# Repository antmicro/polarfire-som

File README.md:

# PolarFire SoM

Copyright (c) 2023-2025 [Antmicro](https://www.antmicro.com)

## Overview

This project contains open hardware design files for the Antmicro PolarFire System on Module (SoM) built around Microchip [PolarFire MPFS250T](https://www.microchip.com/en-us/product/mpfs250t) RISC-V System on Chip.
The SoM exposes two 100-pin high density connectors with signal assignment that is electrically compatible with [Raspberry Pi Compute Module 4](https://datasheets.raspberrypi.com/cm4/cm4-datasheet.pdf).

The PCB design files were prepared in KiCad 7.

## Key features

* PolarFire SoC MPFS250T
* 2 GB LPDDR4-1866 SDRAM
* 8 GB eMMC flash memory
* Compact size: 55x40mm 
* Gigabit Ethernet PHY (Ti/[DP83867ISRGZR](https://www.ti.com/lit/gpn/DP83867IS))
* 4-lane PCIe (via MPFS250T built-in XCVR transceivers)
* 2.4 GHz, 5.0 GHz IEEE 802.11 b/g/n/ac WiFi module (Murata/[LBEE5PK2AE](https://www.murata.com/en-eu/products/connectivitymodule/wi-fi-bluetooth/overview/lineup/type2ae))
* Bluetooth 5.2 module (Murata/LBEE5PK2AE)
* HDMI output
* 4-lane MIPI DSI and 4-lane MIPI CSI-2 exposed via Lattice [CrossLink](https://www.latticesemi.com/Products/FPGAandCPLD/CrossLink) (LIF-MD6000-6JMG80I) companion IC
* Additional 2-lane MIPI CSI-2 camera port, when working in 1.8V logic
* On-board power sequencing and voltage regulation based on a single 5V supply

## Project structure

The main directory contains KiCad PCB project files, a LICENSE, and a README.
The remaining files are stored in the following directories:

* `doc` - contains schematics in PDF format
* `assets` - contains visual assets for showcasing this design on [Open Hardware Portal](https://openhardware.antmicro.com).
* `img` - contains graphics for this README

## Licensing

This project is published under the [Apache-2.0](LICENSE) license.

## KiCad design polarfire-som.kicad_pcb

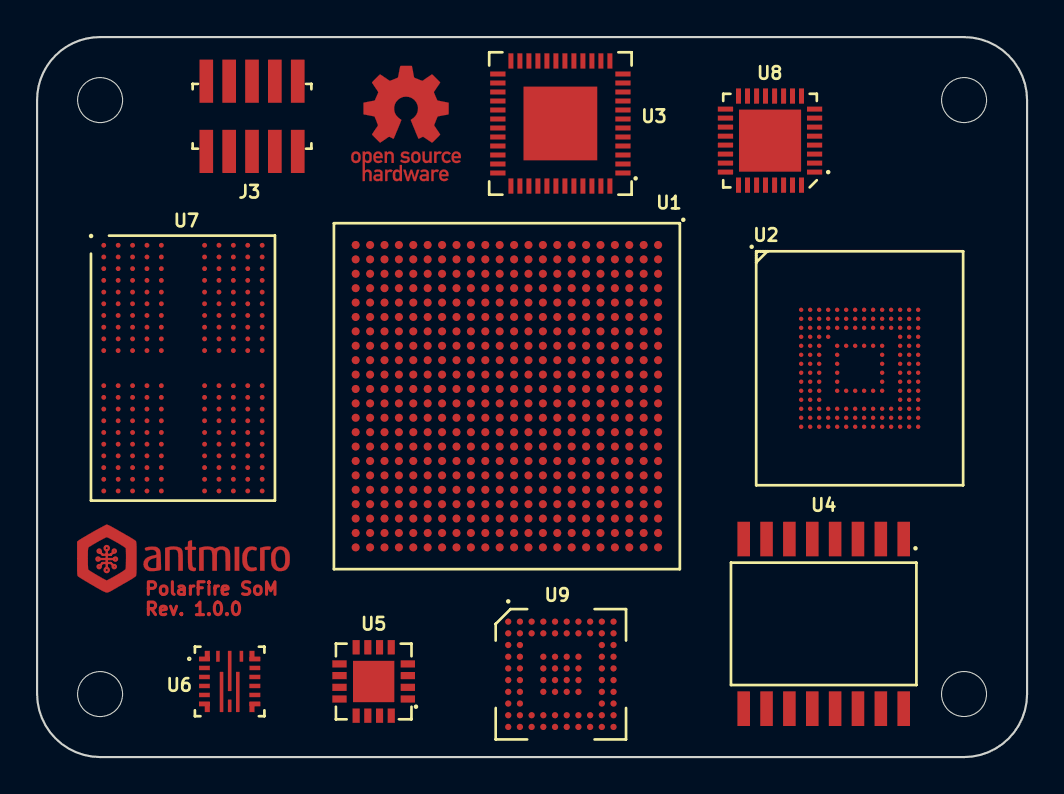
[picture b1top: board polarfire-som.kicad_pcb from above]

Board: 2 copper layers, 55.0 x 40.0 mm, 17 parts (1 on the bottom side), 211 nets, no tracks yet.

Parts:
J1: CM4_Plug_Module_Hirose_DF40_2x50_DF40C-100DP-0.4V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; CM4_Module_Conn_Plug_Hirose_DF40_2x50_DF40C-100DP-0.4V
J3: PinHeader_2x5_P1.27mm_SMD
MP1, MP2, MP3, MP4: MP_NPTH_Drill2.5mm
N1: antmicro_logo; antmicro-logo_scaled_12mm
N2: oshw_logo; oshw-logo
U1: MPFS250T-FCVG484; BGA-484_19x19mm_Layout22x22_P0.8mm_FCVG484
U2: SDINBDG4-8G; BGA-196-153_11.5x13mm_Layout14x14_P0.5x0.5mm
U3: DP83867ISRGZR; VQFN-48_7x7mm_P0.5mm_EP4.1x4.1mm
U4: MT25QL01GBBB8E_SOP2-16; SOP2-16_7.5x10.3mm
U5: PAC1934_QFN; QFN-16-1EP_4x4mm_P0.65mm
U6: TPS65296; VQFN-HR-18_3.5x3.5x1mm
U7: MT53D512M32D2_WFBGA; BGA-200_10.0x14.5mm_Layout12x22_P0.80x0.65mm
U8: USB3300-EZK-TR; QFN-32-1EP_5x5mm
U9: CrossLink_LIF-MD6000-6JMG80I; BGA-80_7x7mm_Layout10x10_P0.65mm

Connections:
/LPDDR4/LPDDR4_CA0_A: U1.T5 (MSS_DDR_A0), U7.H2 (CA0_A), U7.R2 (CA0_B)
/LPDDR4/LPDDR4_CA1_A: U1.T6 (MSS_DDR_A1), U7.J2 (CA1_A), U7.P2 (CA1_B)
/LPDDR4/LPDDR4_CA2_A: U1.V7 (MSS_DDR_A2), U7.H9 (CA2_A), U7.R9 (CA2_B)
/LPDDR4/LPDDR4_CA3_A: U1.V6 (MSS_DDR_A3), U7.H10 (CA3_A), U7.R10 (CA3_B)
/LPDDR4/LPDDR4_CA4_A: U1.R6 (MSS_DDR_A4), U7.H11 (CA4_A), U7.R11 (CA4_B)
/LPDDR4/LPDDR4_CA5_A: U1.R5 (MSS_DDR_A5), U7.J11 (CA5_A), U7.P11 (CA5_B)
/LPDDR4/LPDDR4_CKE0_A: U1.K1 (MSS_DDR_CKE0), U7.J4 (CKE0_A), U7.P4 (CKE0_B)
/LPDDR4/LPDDR4_CK_C_A: U1.U4 (MSS_DDR_CK_N0), U7.J9 (CK_c_A), U7.P9 (CK_c_B)
/LPDDR4/LPDDR4_CK_T_A: U1.U5 (MSS_DDR_CK0/DDR_PLL0_OUT0), U7.J8 (CK_t_A), U7.P8 (CK_t_B)
/LPDDR4/LPDDR4_CS0_A: U1.L3 (MSS_DDR_CS0), U7.H4 (CS0_A), U7.R4 (CS0_B)
/LPDDR4/LPDDR4_DMI0: U1.AB4 (MSS_DDR_DM0), U7.C3 (DMI0_A)
/LPDDR4/LPDDR4_DMI1: U1.AA7 (MSS_DDR_DM1), U7.C10 (DMI1_A)
/LPDDR4/LPDDR4_DMI2: U1.Y10 (MSS_DDR_DM2), U7.Y3 (DMI0_B)
/LPDDR4/LPDDR4_DMI3: U1.T10 (MSS_DDR_DM3), U7.Y10 (DMI1_B)
/LPDDR4/LPDDR4_DQ0: U1.Y3 (MSS_DDR_DQ0), U7.B2 (DQ0_A)
/LPDDR4/LPDDR4_DQ1: U1.Y4 (MSS_DDR_DQ1), U7.C2 (DQ1_A)
/LPDDR4/LPDDR4_DQ2: U1.Y1 (MSS_DDR_DQ2), U7.E2 (DQ2_A)
/LPDDR4/LPDDR4_DQ3: U1.AA1 (MSS_DDR_DQ3), U7.F2 (DQ3_A)
/LPDDR4/LPDDR4_DQ4: U1.Y5 (MSS_DDR_DQ4), U7.F4 (DQ4_A)
/LPDDR4/LPDDR4_DQ5: U1.AA5 (MSS_DDR_DQ5), U7.E4 (DQ5_A)
/LPDDR4/LPDDR4_DQ6: U1.AB2 (MSS_DDR_DQ6), U7.C4 (DQ6_A)
/LPDDR4/LPDDR4_DQ7: U1.AB3 (MSS_DDR_DQ7), U7.B4 (DQ7_A)
/LPDDR4/LPDDR4_DQ8: U1.W8 (MSS_DDR_DQ8), U7.B11 (DQ8_A)
/LPDDR4/LPDDR4_DQ9: U1.W7 (MSS_DDR_DQ9), U7.C11 (DQ9_A)
/LPDDR4/LPDDR4_DQ10: U1.AB5 (MSS_DDR_DQ10), U7.E11 (DQ10_A)
/LPDDR4/LPDDR4_DQ11: U1.AA6 (MSS_DDR_DQ11), U7.F11 (DQ11_A)
/LPDDR4/LPDDR4_DQ12: U1.AB7 (MSS_DDR_DQ12), U7.F9 (DQ12_A)
/LPDDR4/LPDDR4_DQ13: U1.AB8 (MSS_DDR_DQ13), U7.E9 (DQ13_A)
/LPDDR4/LPDDR4_DQ14: U1.Y8 (MSS_DDR_DQ14), U7.C9 (DQ14_A)
/LPDDR4/LPDDR4_DQ15: U1.AA8 (MSS_DDR_DQ15), U7.B9 (DQ15_A)
/LPDDR4/LPDDR4_DQ16: U1.Y9 (MSS_DDR_DQ16), U7.AA2 (DQ0_B)
/LPDDR4/LPDDR4_DQ17: U1.W9 (MSS_DDR_DQ17), U7.Y2 (DQ1_B)
/LPDDR4/LPDDR4_DQ18: U1.AB9 (MSS_DDR_DQ18), U7.V2 (DQ2_B)
/LPDDR4/LPDDR4_DQ19: U1.AB10 (MSS_DDR_DQ19), U7.U2 (DQ3_B)
/LPDDR4/LPDDR4_DQ20: U1.V11 (MSS_DDR_DQ20), U7.U4 (DQ4_B)
/LPDDR4/LPDDR4_DQ21: U1.V10 (MSS_DDR_DQ21), U7.V4 (DQ5_B)
/LPDDR4/LPDDR4_DQ22: U1.Y11 (MSS_DDR_DQ22), U7.Y4 (DQ6_B)
/LPDDR4/LPDDR4_DQ23: U1.W11 (MSS_DDR_DQ23), U7.AA4 (DQ7_B)
/LPDDR4/LPDDR4_DQ24: U1.U8 (MSS_DDR_DQ24), U7.AA11 (DQ8_B)
/LPDDR4/LPDDR4_DQ25: U1.T8 (MSS_DDR_DQ25), U7.Y11 (DQ9_B)
/LPDDR4/LPDDR4_DQ26: U1.T11 (MSS_DDR_DQ26), U7.V11 (DQ10_B)
/LPDDR4/LPDDR4_DQ27: U1.U10 (MSS_DDR_DQ27), U7.U11 (DQ11_B)
/LPDDR4/LPDDR4_DQ28: U1.R11 (MSS_DDR_DQ28), U7.U9 (DQ12_B)
/LPDDR4/LPDDR4_DQ29: U1.R10 (MSS_DDR_DQ29), U7.V9 (DQ13_B)
/LPDDR4/LPDDR4_DQ30: U1.R8 (MSS_DDR_DQ30), U7.Y9 (DQ14_B)
/LPDDR4/LPDDR4_DQ31: U1.P8 (MSS_DDR_DQ31), U7.AA9 (DQ15_B)
/LPDDR4/LPDDR4_DQS0_N: U1.AA3 (MSS_DDR_DQS_N0), U7.E3 (DQS0_c_A)
/LPDDR4/LPDDR4_DQS0_P: U1.AA2 (MSS_DDR_DQS_P0), U7.D3 (DQS0_t_A)
/LPDDR4/LPDDR4_DQS1_N: U1.W6 (MSS_DDR_DQS_N1), U7.E10 (DQS1_c_A)
/LPDDR4/LPDDR4_DQS1_P: U1.Y6 (MSS_DDR_DQS_P1), U7.D10 (DQS1_t_A)
/LPDDR4/LPDDR4_DQS2_N: U1.AA10 (MSS_DDR_DQS_N2), U7.V3 (DQS0_c_B)
/LPDDR4/LPDDR4_DQS2_P: U1.AA11 (MSS_DDR_DQS_P2), U7.W3 (DQS0_t_B)
/LPDDR4/LPDDR4_DQS3_N: U1.V9 (MSS_DDR_DQS_N3), U7.V10 (DQS1_c_B)
/LPDDR4/LPDDR4_DQS3_P: U1.U9 (MSS_DDR_DQS_P3), U7.W10 (DQS1_t_B)
/LPDDR4/LPDDR4_ODT_CA_A: U1.L1 (MSS_DDR_ODT0), U7.G2 (ODT_CA_A), U7.T2 (ODT_CA_B)
/LPDDR4/LPDDR4_RESET_n: U1.L2 (MSS_DDR_RAM_RST_N/DDR_PLL0_OUT1), U7.T11 (RESET_n)
CAM1_C_N: J1.127, U9.A8 (DPHY0_CKN)
CAM1_C_P: J1.129, U9.B8 (DPHY0_CKP)
CAM1_D0_N: J1.115, U9.A7 (DPHY0_DN0)
CAM1_D0_P: J1.117, U9.B7 (DPHY0_DP0)
CAM1_D1_N: J1.121, U9.A9 (DPHY0_DN1)
CAM1_D1_P: J1.123, U9.B9 (DPHY0_DP1)
CAM1_D2_N: J1.133, U9.A6 (DPHY0_DN2)
CAM1_D2_P: J1.135, U9.B6 (DPHY0_DP2)
CAM1_D3_N: J1.139, U9.A10 (DPHY0_DN3)
CAM1_D3_P: J1.141, U9.B10 (DPHY0_DP3)
DSI1_C_N: J1.187, U9.A3 (DPHY1_CKN)
DSI1_C_P: J1.189, U9.B3 (DPHY1_CKP)
DSI1_D0_N: J1.175, U9.A2 (DPHY1_DN0)
DSI1_D0_P: J1.177, U9.B2 (DPHY1_DP0)
DSI1_D1_N: J1.181, U9.A4 (DPHY1_DN1)
DSI1_D1_P: J1.183, U9.B4 (DPHY1_DP1)
DSI1_D2_N: J1.193, U9.A1 (DPHY1_DN2)
DSI1_D2_P: J1.195, U9.B1 (DPHY1_DP2)
DSI1_D3_N: J1.194, U9.B5 (DPHY1_DP3)
DSI1_D3_P: J1.196, U9.A5 (DPHY1_DN3)
ETH_ TXRXM_C: J1.9, U3.8 (TD_M_C)
ETH_ TXRXM_D: J1.5, U3.11 (TD_M_D)
ETH_ TXRXP_B: J1.4, U3.4 (TD_P_B)
ETH_ TXRXP_D: J1.3, U3.10 (TD_P_D)
ETH_LED1: J1.15, U3.47 (LED_0)
ETH_LED2: J1.17, U3.46 (LED_1)
ETH_TXRXM_A: J1.10, U3.2 (TD_M_A)
ETH_TXRXM_B: J1.6, U3.5 (TD_M_B)
ETH_TXRXP_A: J1.12, U3.1 (TD_P_A)
ETH_TXRXP_C: J1.11, U3.7 (TD_P_C)
GND: J1.1, J1.2, J1.7, J1.8, J1.13, J1.14, J1.22, J1.23, J1.32, J1.33, J1.42, J1.43, J1.52, J1.53, J1.59, J1.60, J1.65, J1.71, J1.74, J1.98, J1.107, J1.108, J1.113, J1.114, J1.119, J1.120, J1.125, J1.126, J1.131, J1.132, J1.137, J1.138, J1.150, J1.155, J1.156, J1.161, J1.162, J1.167, J1.168, J1.173, J1.174, J1.179, J1.180, J1.185, J1.186
GPIO2: J1.58, U1.A8 (GPIO175PB1)
GPIO3: J1.56, U1.B8 (GPIO175NB1)
GPIO4: J1.54, U1.A6 (GPIO172PB1/CCC_SW_PLL1_OUT1)
GPIO5: J1.34, U1.C9 (GPIO176NB1/DQS)
GPIO6: J1.30, U1.D8 (GPIO174NB1)
GPIO7: J1.37, U1.H13 (GPIO185NB1)
GPIO8: J1.39, U1.H12 (GPIO182PB1/DQS)
GPIO9: J1.40, U1.G12 (GPIO182NB1/DQS)
GPIO10: J1.44, U1.D13 (GPIO2PB1/DQS)
GPIO11: J1.38, U1.C10 (GPIO176PB1/DQS/CCC_SW_PLL0_OUT0)
GPIO12: J1.31, U1.D9 (GPIO174PB1)
GPIO13: J1.28, U1.D6 (GPIO168NB1)
GPIO14: J1.55, U1.A7 (GPIO173PB1/CLKIN_S_3/CCC_SW_CLKIN_S_3)
GPIO15: J1.51, U1.H15 (GPIO7NB1)
GPIO16: J1.29, U1.C6 (GPIO171PB1/CLKIN_S_2/CCC_SW_CLKIN_S_2/C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)
GPIO17: J1.50, U1.H17 (GPIO8NB1/DQS)
GPIO18: J1.49, U1.G15 (GPIO7PB1)
GPIO19: J1.26, U1.B5 (GPIO170NB1/DQS)
GPIO20: J1.27, U1.C5 (GPIO170PB1/DQS/CCC_SW_PLL1_OUT0)
GPIO21: J1.25, U1.C4 (GPIO169PB1/CCC_SW_CLKIN_S_1)
GPIO22: J1.46, U1.F11 (GPIO181NB1)
GPIO23: J1.47, U1.F16 (GPIO11NB1)
GPIO24: J1.45, U1.D14 (GPIO2NB1/DQS)
GPIO25: J1.41, U1.E14 (GPIO9NB1)
GPIO26: J1.24, U1.B4 (GPIO169NB1)
GPIO27: J1.48, U1.G17 (GPIO8PB1/DQS/CCC_SE_PLL0_OUT0)
JTAG_RESET_n: J3.10, U1.H7 (DEVRST_N)
JTAG_TCK: J3.4, U1.E9 (TCK)
JTAG_TDI: J3.8, U1.G9 (TDI)
JTAG_TDO: J3.6, U1.E8 (TDO)
JTAG_TMS: J3.2, U1.F8 (TMS)
MSS_SGMII_RX0_N: U1.L6 (MSS_SGMII_RXN0), U3.36 (RX_D3_SGMII_SON)
MSS_SGMII_RX0_P: U1.L5 (MSS_SGMII_RXP0), U3.35 (RX_D2_SGMII_SOP)
MSS_SGMII_TX0_N: U1.N6 (MSS_SGMII_TXP0), U3.28 (TX_D0_SGMII_SIN)
MSS_SGMII_TX0_P: U1.N7 (MSS_SGMII_TXN0), U3.27 (TX_D1_SGMII_SIP)
unnamed: U1.A1 (VSS), U1.A4 (VSS), U1.A14 (VSS), U1.A22 (VSS), U1.AA4 (VSS), U1.AA14 (VSS), U1.AB1 (VSS), U1.AB11 (VSS), U1.AB22 (VSS), U1.B11 (VSS), U1.C8 (VSS), U1.C18 (VSS), U1.D5 (VSS), U1.D15 (VSS), U1.E2 (VSS), U1.E12 (VSS), U1.E20 (VSS), U1.E21 (VSS), U1.E22 (VSS), U1.F9 (VSS), U1.F18 (VSS), U1.F19 (VSS), U1.F20 (VSS), U1.G6 (VSS), U1.G16 (VSS), U1.G18 (VSS), U1.G22 (VSS), U1.H3 (VSS), U1.H20 (VSS), U1.J8 (VSS), U1.J10 (VSS), U1.J12 (VSS), U1.J14 (VSS), U1.J16 (VSS), U1.J22 (VSS), U1.K9 (VSS), U1.K11 (VSS), U1.K13 (VSS), U1.K15 (VSS), U1.K17 (VSS), U1.K20 (VSS), U1.L4 (VSS), U1.L10 (VSS), U1.L12 (VSS), U1.L14 (VSS), U1.L16 (VSS), U1.L18 (VSS), U1.L22 (VSS), U1.M1 (VSS), U1.M9 (VSS), U1.M11 (VSS), U1.M13 (VSS), U1.M15 (VSS), U1.M17 (VSS), U1.M19 (VSS), U1.M20 (VSS), U1.N10 (VSS), U1.N12 (VSS), U1.N14 (VSS), U1.N16 (VSS), U1.N18 (VSS), U1.N22 (VSS), U1.P5 (VSS), U1.P9 (VSS), U1.P11 (VSS), U1.P13 (VSS), U1.P15 (VSS), U1.P17 (VSS), U1.P20 (VSS), U1.R2 (VSS), U1.R18 (VSS), U1.R22 (VSS), U1.T9 (VSS), U1.T18 (VSS), U1.T19 (VSS), U1.T20 (VSS), U1.U6 (VSS), U1.U16 (VSS), U1.U20 (VSS), U1.U21 (VSS), U1.U22 (VSS), U1.V3 (VSS), U1.V13 (VSS), U1.W10 (VSS), U1.W20 (VSS), U1.Y7 (VSS), U1.Y17 (VSS)
unnamed: U1.A9 (VDDI1), U1.A19 (VDDI1), U1.B6 (VDDI1), U1.B16 (VDDI1), U1.C13 (VDDI1), U1.C21 (VDDI1), U1.D10 (VDDI1), U1.E17 (VDDI1), U1.F14 (VDDI1), U1.G11 (VDDI1)
unnamed: U1.AA9 (VDDI6), U1.AB6 (VDDI6), U1.N3 (VDDI6), U1.R7 (VDDI6), U1.T4 (VDDI6), U1.U1 (VDDI6), U1.U11 (VDDI6), U1.V8 (VDDI6), U1.W5 (VDDI6), U1.Y2 (VDDI6)
unnamed: U1.AA19 (VDDI0), U1.AB16 (VDDI0), U1.T14 (VDDI0), U1.V18 (VDDI0), U1.W15 (VDDI0), U1.Y12 (VDDI0), U1.Y22 (VDDI0)
unnamed: U1.C3 (VDDI2), U1.F4 (VDDI2), U1.G1 (VDDI2)
unnamed: U1.E7 (VDDI3), U1.J11 (VDDI3)
unnamed: U1.G21 (VDDA), U1.J21 (VDDA), U1.K19 (VDDA), U1.L21 (VDDA), U1.N21 (VDDA), U1.P19 (VDDA), U1.R21 (VDDA)
unnamed: U1.H8 (VDD25), U1.J17 (VDD25), U1.L15 (VDD25), U1.R9 (VDD25), U1.R17 (VDD25)
unnamed: U1.H14 (VDDAUX1), U1.H16 (VDDAUX1), U1.J9 (VDDAUX1), U1.J13 (VDDAUX1), U1.K10 (VDDAUX1)
unnamed: U1.H18 (XCVR_VREF), U1.H19 (XCVR_VREF)
unnamed: U1.J5 (VDDI4), U1.K2 (VDDI4)
unnamed: U1.J15 (VDD), U1.K12 (VDD), U1.K14 (VDD), U1.K16 (VDD), U1.L11 (VDD), U1.L13 (VDD), U1.L17 (VDD), U1.M12 (VDD), U1.M14 (VDD), U1.M16 (VDD), U1.N11 (VDD), U1.N13 (VDD), U1.N15 (VDD), U1.N17 (VDD)
unnamed: U1.J18 (VDDA25), U1.M18 (VDDA25)
unnamed: U1.K8 (VDDAUX2), U1.L9 (VDDAUX2)
unnamed: U1.K18 (VDD_XCVR_CLK), U1.P18 (VDD_XCVR_CLK)
unnamed: U1.M6 (VDDI5), U1.M8 (VDDI5)
unnamed: U1.M10 (VDDAUX4), U1.N9 (VDDAUX4)
unnamed: U1.P10 (VDD18), U1.P12 (VDD18), U1.P14 (VDD18), U1.P16 (VDD18), U1.R13 (VDD18)
unnamed: U2.A6 (VSS), U2.E7 (VSS), U2.G5 (VSS), U2.H10 (VSS), U2.J5 (VSS), U2.K8 (VSS)
unnamed: U2.C4 (VSSQ), U2.N2 (VSSQ), U2.N5 (VSSQ), U2.P4 (VSSQ), U2.P6 (VSSQ)
unnamed: U2.C6 (VCCQ), U2.M4 (VCCQ), U2.N4 (VCCQ), U2.P3 (VCCQ), U2.P5 (VCCQ)
unnamed: U2.E6 (VCC), U2.F5 (VCC), U2.J10 (VCC), U2.K9 (VCC)
unnamed: U3.3 (VDDA2P5), U3.9 (VDDA2P5)
unnamed: U3.13 (VDDA1P8), U3.48 (VDDA1P8)
unnamed: U3.19 (VDDIO), U3.30 (VDDIO), U3.41 (VDDIO)
unnamed: U3.6 (VDD1P0), U3.24 (VDD1P0), U3.31 (VDD1P0), U3.42 (VDD1P0)
unnamed: U7.A3 (VSS), U7.C1 (VSS), U7.C5 (VSS), U7.C8 (VSS), U7.D2 (VSS), U7.D4 (VSS), U7.D9 (VSS), U7.E1 (VSS), U7.E5 (VSS), U7.E8 (VSS), U7.G1 (VSS), U7.G3 (VSS), U7.G5 (VSS), U7.G8 (VSS), U7.J1 (VSS), U7.J3 (VSS), U7.K2 (VSS), U7.K4 (VSS), U7.K9 (VSS), U7.N2 (VSS), U7.N4 (VSS), U7.N9 (VSS), U7.P1 (VSS), U7.P3 (VSS), U7.T1 (VSS), U7.T3 (VSS), U7.T5 (VSS), U7.T8 (VSS)
unnamed: U7.A4 (VDD2), U7.A9 (VDD2), U7.F5 (VDD2), U7.F8 (VDD2), U7.H1 (VDD2), U7.H5 (VDD2), U7.H8 (VDD2), U7.K1 (VDD2), U7.K3 (VDD2), U7.N1 (VDD2), U7.N3 (VDD2), U7.R1 (VDD2), U7.R5 (VDD2), U7.R8 (VDD2)
unnamed: U7.A10 (VSS), U7.AB3 (VSS), U7.AB5 (VSS), U7.AB8 (VSS), U7.AB10 (VSS), U7.C12 (VSS), U7.D11 (VSS), U7.E12 (VSS), U7.G10 (VSS), U7.G12 (VSS), U7.J10 (VSS), U7.J12 (VSS), U7.K11 (VSS), U7.N11 (VSS), U7.P10 (VSS), U7.P12 (VSS), U7.T10 (VSS), U7.T12 (VSS), U7.V1 (VSS), U7.V5 (VSS), U7.V8 (VSS), U7.V12 (VSS), U7.W2 (VSS), U7.W4 (VSS), U7.W9 (VSS), U7.W11 (VSS), U7.Y1 (VSS), U7.Y5 (VSS), U7.Y8 (VSS), U7.Y12 (VSS)
unnamed: U7.AA3 (VDDQ), U7.AA5 (VDDQ), U7.AA8 (VDDQ), U7.AA10 (VDDQ), U7.B10 (VDDQ), U7.D12 (VDDQ), U7.F10 (VDDQ), U7.U3 (VDDQ), U7.U10 (VDDQ), U7.W1 (VDDQ), U7.W5 (VDDQ), U7.W8 (VDDQ), U7.W12 (VDDQ)
unnamed: U7.AB4 (VDD2), U7.AB9 (VDD2), U7.H12 (VDD2), U7.K10 (VDD2), U7.K12 (VDD2), U7.N10 (VDD2), U7.N12 (VDD2), U7.R12 (VDD2), U7.U5 (VDD2), U7.U8 (VDD2)
unnamed: U7.B3 (VDDQ), U7.B5 (VDDQ), U7.B8 (VDDQ), U7.D1 (VDDQ), U7.D5 (VDDQ), U7.D8 (VDDQ), U7.F3 (VDDQ)
unnamed: U7.F1 (VDD1), U7.G4 (VDD1), U7.G9 (VDD1), U7.T4 (VDD1), U7.T9 (VDD1), U7.U1 (VDD1)
unnamed: U7.F12 (VDD1), U7.U12 (VDD1)
unnamed: U8.1 (GND), U8.2 (GND), U8.33 (EP)
unnamed: U8.15 (VDD1.8), U8.26 (VDD1.8)
unnamed: U8.6 (VDD3.3), U8.16 (VDD3.3), U8.25 (VDD3.3), U8.30 (VDD3.3)
unnamed: U9.C1 (GND), U9.C10 (GND), U9.E5 (GND), U9.G2 (GND), U9.G5 (GND)
unnamed: U9.E4 (VCC), U9.E6 (VCC)
unnamed: U9.F5 (VCCIO1), U9.G4 (VCCIO1)
unnamed: U9.F6 (VCCIO2), U9.F7 (VCCIO2)
PAC1934_SCL: U1.F12 (GPIO181PB1), U5.4 (SM_CLK)
PAC1934_SDA: U1.F13 (GPIO184NB1), U5.5 (SM_DATA)
PCIe_CLK_N: J1.112, U1.L20 (XCVR_0A_REFCLK_N)
PCIe_CLK_P: J1.110, U1.L19 (XCVR_0A_REFCLK_P)
PCIe_RX1_N: J1.118, U1.G19 (XCVR_0_RX0_N)
PCIe_RX1_P: J1.116, U1.G20 (XCVR_0_RX0_P)
PCIe_RX2_N: J1.154, U1.K21 (XCVR_0_RX1_N)
PCIe_RX2_P: J1.152, U1.K22 (XCVR_0_RX1_P)
PCIe_RX3_N: J1.157, U1.M22 (XCVR_0_RX2_P)
PCIe_RX3_P: J1.159, U1.M21 (XCVR_0_RX2_N)
PCIe_RX4_N: J1.166, U1.R19 (XCVR_0_RX3_N)
PCIe_RX4_P: J1.164, U1.R20 (XCVR_0_RX3_P)
PCIe_TX1_N: J1.124, U1.F21 (XCVR_0_TX0_N)
PCIe_TX1_P: J1.122, U1.F22 (XCVR_0_TX0_P)
PCIe_TX2_N: J1.148, U1.H21 (XCVR_0_TX1_N)
PCIe_TX2_P: J1.146, U1.H22 (XCVR_0_TX1_P)
PCIe_TX3_N: J1.160, U1.P21 (XCVR_0_TX2_N)
PCIe_TX3_P: J1.158, U1.P22 (XCVR_0_TX2_P)
PCIe_TX4_N: J1.163, U1.T22 (XCVR_0_TX3_P)
PCIe_TX4_P: J1.165, U1.T21 (XCVR_0_TX3_N)
SC_SPI_MISO: U1.H10 (SDI), U4.8 (DQ1)
SC_SPI_MOSI: U1.F7 (SDO), U4.15 (DQ0)
SC_SPI_SCK: U1.E6 (SCK), U4.16 (C)
SC_SPI_SS: U1.G7 (SS), U4.7 (S#)
SD_CLK: J1.57, U1.J1 (MSSIO0B4), U2.M6 (CLK)
SD_DAT0: J1.63, U1.H1 (MSSIO2B4), U2.A3 (DAT0)
SD_DAT1: J1.67, U1.J4 (MSSIO3B4), U2.A4 (DAT1)
SD_DAT2: J1.69, U1.K4 (MSSIO4B4), U2.A5 (DAT2)
SD_DAT3: J1.61, U1.J7 (MSSIO5B4), U2.B2 (DAT3)
SD_DAT4: J1.68, U1.J6 (MSSIO8B4), U2.B3 (DAT4)
SD_DAT5: J1.64, U1.H6 (MSSIO9B4), U2.B4 (DAT5)
SD_DAT6: J1.72, U1.J3 (MSSIO10B4), U2.B5 (DAT6)
SD_DAT7: J1.70, U1.H2 (MSSIO11B4), U2.B6 (DAT7)
USB_CLK: U1.G4 (MSSIO17B2), U8.14 (CLKOUT)
USB_DATA_0: U1.F2 (MSSIO18B2), U8.24 (DATA[0])
USB_DATA_1: U1.E1 (MSSIO19B2), U8.23 (DATA[1])
USB_DATA_2: U1.G3 (MSSIO20B2), U8.22 (DATA[2])
USB_DATA_3: U1.F5 (MSSIO21B2), U8.21 (DATA[3])
USB_DATA_4: U1.D1 (MSSIO22B2), U8.20 (DATA[4])
USB_DATA_5: U1.D2 (MSSIO23B2), U8.19 (DATA[5])
USB_DATA_6: U1.F6 (MSSIO24B2), U8.18 (DATA[6])
USB_DATA_7: U1.F3 (MSSIO25B2), U8.17 (DATA[7])
USB_DIR: U1.F1 (MSSIO15B2), U8.12 (DIR)
USB_N: J1.103, U8.8 (DM)
USB_NXT: U1.G2 (MSSIO14B2), U8.11 (NXT)
USB_OTG_ID: J1.101, U8.5 (ID)
USB_P: J1.105, U8.7 (DP)
USB_STP: U1.G5 (MSSIO16B2), U8.13 (STP)

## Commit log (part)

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2024-01-17 [#52579] Updatae cm4 connector module footprint
2024-01-17 [#52579] Change JTAG conn to FTSH-105-01-F-DV
2024-01-19 [#53847] Add TPD12S016 and connect HDMI to pfsom
2024-01-19 [#52577] Add power mux for bank 1, 2 and 4 supply
2024-01-19 [#54013] Add eMMC pullup resistors
2024-01-19 [#54013] Add eMMC decoupling capacitors
2024-01-19 [#53847] Add MIPI25 implementation of PF SoC
2024-01-19 [#53847] Add PCLK to Crosslink data transmission
2024-01-19 [#52577] Clear annotations
2024-01-19 [#54013] Add resistor array
2024-01-19 [#53847] Connect PF SoC to CrossLink
2024-01-19 [#52577] Update PMIC's PVINVTT supply and GPO3 pullup
2024-01-19 [#54016] Add decoupling capacitors
    [#54016] Place decoupling capacitors at SoC sub-sheet
2024-01-19 [#54016] Connect power to PolarFire SoC
2024-01-22 [#54016] Connect power to CrossLink
2024-01-22 [#54016] Connect power to Ethernet PHY
2024-01-22 [#54016] Update CrossLink's power filtering
2024-01-22 [#54016] Add power to connectors
2024-01-22 [#54016] Connect power to SPI FLASH
2024-01-26 [#53979] Resolve ethernet pin mapping
2024-01-26 [#54041] Add pre-commit to .gitignore
2024-01-26 [#54202] Update PF BANK1 with alternative pin labels
2024-01-26 [#53979] Reassign ethernet LEDs
2024-01-26 [#54041] Add USB components
2024-02-19 [#54016] Place components to assess available space
2024-02-19 [#54016] Change boost converter inductor
2024-02-19 [#53847] Reconnect ETH sync pins to DP83867ISRGZR GPIOs
2024-02-19 [#54442] Connect ethernet management interface
2024-02-19 [#54442] Add SGMII routing guidelines
2024-02-19 [#54442] Add crystal to ethernet transceiver
2024-02-19 [#54016] Update Bank 5 voltage
2024-02-19 [#54272] Change MT25QL01GBBB package
2024-02-19 [#54442] Pull-down unused transceiver pins
2024-02-19 [#54491] Provide power for LPDDR4
2024-02-19 [#54491] Connect PCIe_RST and I2C to PF
2024-02-19 [#54016] Connect power monitor
2024-02-19 [#54178] Add WiFi subsheet
2024-02-19 [#54178] Add sleep clock
2024-02-19 [#54178] Add WiFi module with adjacent components
2024-02-19 [#54491] Exclude DNP from BOM
2024-02-19 [#54178] Add WL and BT disable to WiFi module
2024-02-19 [#54178] Place added components on PCB
2024-02-19 [#54178] Add JTAG chain, rename WiFi subsheet
2024-02-19 [#54828] Add connections and external components to USB hub
2024-02-19 [#54491] Change VBAT in USB Phy to 3V3
2024-02-19 [#54828] Add USB hub, change LBEE5PK2AE connection to USB
2024-02-19 [#54491] Annotate schematics
2024-02-19 [#54491] Update JTAG TRSTB connection to Bank 3
2024-02-19 [#53847] Change NTS0104BQ to NTS0104UK
2024-02-19 [#54899] Update symbols
2024-02-19 [#54899] Simplify CrossLink's power filtering
2024-02-19 [#55288] Change Ethernet PHY crystal to oscillator
2024-02-19 [#54822] Mark unused pins of MIPI CrossLink
2024-02-19 [#55275] Implement MIPI on GPIO
2024-02-19 [#54899] Change Bank 3 power supply to +3V3
2024-02-19 [#54899] Add NC flag to Bank 5 of MPFS250T
2024-02-19 [#54899] Add power sequencing to Power Mux
2024-02-19 [#54899] Change Ethernet PHY power configuration to Two-Supply
2024-02-19 [#54899] Add jumper on +2V5 line
2024-02-19 [#54899] Simplify power sequencing, add missing connections
2024-02-19 [#54899] Add backup UART and SDIO to WiFi module
2024-02-19 [#53847] Add HDMI
    [#53847] Add HDMI driver power decoupling
2024-02-19 [#55232] Change USB PHY and HUB
2024-02-19 [#54899] Re-annotate components
2024-02-19 [#53847] Replace SN74LVC1T with SN74LVC1T45YZPR
2024-02-19 [#53847] Add HDMI level shifters
2024-02-19 [#54899] Change ETH labels to differential
2024-02-19 [#54899] Flag not connected pins
2024-02-19 [#54822] Add resistor to CRESET_B pin of MIPI CrossLink
2024-02-19 [#55288] Update CrossLink's power supply and filtering
2024-02-19 [#54899] Replace 330u capacitors
2024-02-19 [#54016] Connect VDDSREF decoupling capacitors
2024-02-19 [#54016] Add PAC1934 to MSSIO I2C_1, change USB hub default address
2024-02-19 [#54899] Update USB labels and positions
    [#54899] Update pin types and ULPI regulators capacitors
2024-02-19 [#54899] Update level shifters symbols to glb libs
2024-02-19 [#53847] Add SN75DP159RSBT to HDMI schematic
2024-02-19 [#54899] Add R128
2024-02-19 [#55197] Connect HDMI to PF Bank 1
2024-02-19 [#54491] Fix crystal calculations typo
2024-02-19 [#55288] Change SoC decoupling capacitors to 0201
2024-02-19 [#54899] Connect unused Ethernet PHY pins according to reference design
2024-02-19 [#53847] Pull-up CEC to 3V3
2024-02-19 [#55288] Replace PMIC, create initial placement
2024-02-19 [#55288] Change LPDDR4 power supply to +1V1
2024-02-19 [#55288] Replace Tag-Connect with test points
2024-02-19 [#55288] Add programmable 1V8 supply to CrossLink
2024-02-19 [#55401] Add VBUS control
2024-02-19 [#55401] Update visualization
2024-02-19 [#54899] Swap USB lines
2024-02-19 [#55288] Create fanout
2024-02-19 [#54899] Add memory supply logic
2024-02-19 [#55288] Place components for visualization
2024-02-19 [#55401] Update schematics and PCB information
2024-02-19 [#55401] Update layer stack
2024-02-19 [#55401] Add PCB SHA
2024-02-19 [#55401] Update HDMI subsheet's size
2024-02-19 [#55401] Add doc
2024-02-20 [#55401] Enable markings rendering
2024-02-20 [#55401] Update OHP release assets
2024-02-21 Cleanup
2024-02-26 [#55401] Update symbols and footprints
2024-02-27 [#55289] Add labels to SGMII lines
2024-02-27 [#55289] Align fanout
2024-02-27 [#55289] Second connector fanout
2024-02-27 [#55289] ETH fanout
2024-02-27 [#55289] Change eMMC 100n capacitors to 0402
2024-02-27 [#55289] Improve J1 fanout, reposition Polarfire and DDR, create try-on EMCC fanout
2024-02-27 [#55289] Reduce eMMC decoupling
2024-02-27 [#55289] Improve ETH fanout
2024-02-27 [#55289] Simplify LPPDR4 decoupling
2024-02-28 [#55289] Create LPDDR4 fanout
2024-02-28 [#55869] CrossLink fanout
2024-02-28 [#55869] Clear LPDDR4 fanout
2024-02-28 [#55869] Update Vias
2024-03-01 [#55926] Reorder pins on memory selection resistor arrays
2024-03-01 [#55992] Simplify CrossLink's power filtering
2024-03-04 [#55992] Component placement
2024-03-04 [#55992] Rename WL_BT_USB
2024-03-05 [#55690] Add LEDs
2024-03-05 [#55690] Update visualization
2024-03-05 [#55690] Update assets and doc
2024-03-05 [#56060] Update PMIC layout
2024-03-05 [#56060] Create power monitor layout
2024-03-05 [#56060] Update power monitor, place HDMI
2024-03-06 [#56156] Adjust USB circuitry position
2024-03-06 [#55992] Move Flash and WL_BT module down
2024-03-06 [#55690] Swap user LED channels
2024-03-06 [#55289] Add HDMI, PCIe and CSI fanout
2024-03-06 [#55860] Add HDMI ferrite bead
2024-03-07 [#55860] Update HDMI driver symbol
2024-03-07 [#56060] Place decoupling under FPGA
2024-03-08 [#56060] Place decoupling under Crosslink, connect ferrite beads
2024-03-08 [#56060] Fix GND via to RESETB clereance
2024-03-08 [#56060] Finish Crosslink PDN
2024-03-08 [#56060] Connect power monitor and ideal diode
2024-03-11 [#55869] Connect LPDDR4 LS signals
2024-03-11 [#56060] Reduce decoupling
2024-03-11 [#55992] Connect USER LED and PWRON
2024-03-11 [#56232] Replace WL_BT module's inductor
2024-03-12 Start routing Crosslink to PolarFire interface, reroute HDMI
2024-03-12 [#56060] Add power planes
2024-03-12 [#56434] Migrate PCB to 12 layers
2024-03-12 [#56466] Connect JTAG
2024-03-13 [#56466] Try to connect GPIO
2024-03-13 [#56434] Update rules for 14 layers
2024-03-13 [#56434] Update HDMI In2.Cu tracks width
2024-03-13 [#56434] Update PCIe In2.Cu tracks width
2024-03-13 [#56434] Update USB In2.Cu tracks width
2024-03-13 [#56434] Update LPDDR_DQS In4.Cu tracks width
2024-03-13 [#56434] Update PCIe In4.Cu tracks width
2024-03-14 [#56434] Update clearance
2024-03-14 [#56434] Update In2.Cu single-ended tracks width
2024-03-14 [#56434] Update In9.Cu single-ended tracks width
2024-03-14 [#56434] Add 2 layers between 7th and 8th layer
2024-03-14 [#56434] Update rules and pre-defined track widths
2024-03-14 [#56466] Prepare In7.Cu for routing
2024-03-14 [#56466] Connect ETH, JTAG and PCIe LS signals
2024-03-14 [#56466] Rearrange and connect ideal diode, memory supply logic and I2C level shifter
2024-03-15 [#56466] Update CrossLink's connection
2024-03-15 [#56466] Add missing CSI and HDMI lines
2024-03-15 [#56466] Add Edge-Connect, restore JTAG chain
2024-03-18 [#56466] Continue routing LS
2024-03-18 Connect remaining power, continue routing LS
2024-03-18 [#56466] Continue routing LS, add second 1V05 plane
2024-03-19 [#56466] Add GND planes and cutout around WL connector
2024-03-19 [#56466] Connect remaining VDDI, HDMI signals
2024-03-19 [#56466] Finish routing
2024-03-19 [#56715] LPDDR4 match first DQ/DQS group
2024-03-19 [#56715] Match PCIe bottom layer lanes
2024-03-19 [#56715] LPDDR4 match second DQ/DQS group
2024-03-19 [#56715] LPDDR4 match fourth DQ/DQS group
2024-03-19 [#56715] Improve DSI1 matching
2024-03-20 [#56715] Length match ULPI, SPI flash
2024-03-20 [#56715] LPDDR4 match LS signals
2024-03-20 [#56715] Deskew USB. Improve ULPI matching
2024-03-20 [#56784] Update PAC-1934 symbol
2024-03-21 [#56715] Match HDMI0 length
2024-03-21 [#56715] Match PI3HDX511F length
2024-03-21 [#56715] Deskew DSI1_D2
2024-03-21 [#56715] Match CAM1 length
2024-03-21 [#56715] Match DSI1 clock
2024-03-21 [#56715] Add silkscreen
2024-03-21 [#56715] Match Crosslink bank 1
2024-03-21 [#56715] Match SDIO
2024-03-22 [#56715] Clean DRC
2024-03-22 [#56715] Match SD and MEM
2024-03-26 [#56952] Start placing reference designators on bottom side
2024-03-26 [#56952] Finish bottom reference designators placement
2024-03-26 [#56952] Update bottom designators
2024-03-26 [#56952] Adjust top designators
2024-03-27 Update visualization
2024-04-02 README: Minor fix
2024-04-03 [#57422] Add 0R resistors on SENSE+ lines, swap USB lines
2024-04-03 [#57422] Connect VREF_FLAG to Bank 1
2024-04-03 [#57422] Update PI_LED_nPWR pin connection
2024-04-03 [#57422] Apply changes to PCB
2024-04-03 [#57505] Start reworking schematic to hierarchical structure
2024-04-04 [#57422] Add level shifters to WL_BT SDIO
2024-04-04 [#57422] Update USB OTG switching
2024-04-05 [#57422] Improve isolation between power planes, add ETH PHY strap, add fiducials
2024-04-05 [#57422] Add SGMII vias, match XCVR_TX, remove BYP_EN
2024-04-05 [#57505] Finish defining buses
2024-04-05 [#57422] Update PCB
2024-04-05 [#57422] Change WL_BT modules VDDIO to 3V3
2024-04-05 [#57505] Align designators
2024-04-05 [#57505] Implement changes from schematics
2024-04-05 [#57422] Clean DRC
2024-04-08 [#57422] Update capacitor values
2024-04-08 [#57422] Finishing touches
2024-04-11 [#57422] Align schematics
2024-04-11 [#57422] Update img
2024-04-12 [#57970] Update SD connection
2024-05-14 [#59346] Fix typo in README.md
2024-05-15 [#59446] Add Q5-Q8 to BOM
2024-05-17 [#59457] Optimize BOM
2024-05-27 [#59450] Remove custom CM4 connector, add CM4 outline with regular DF40C-100DP-0.4V(51) connectors
2024-05-27 [#59910] Add +3V3 testpoint near Tag-Connect
2024-06-04 [#60204] Add pull-down on LPDDR4 RESET_n
2024-06-05 [#60500] Change ULPI.RESET connection, align schematics
2024-06-07 [#60587] Update UART3 and UART5 nets
2024-06-10 [#60585] Update SCH and PCB revision
2024-06-12 [#59910] Change Tag-Connect to 10 pin
2024-06-12 [#59910] Update Tag-Connect on PCB
2024-06-12 [#59910] Align silkscreen
2024-06-13 [#60905] Update silkscreen around mounting holes
2024-06-14 [#60905] Update OHP assets
2024-06-18 [#61118] Update doc
2024-08-06 [#63104] Add ortho photos
2025-02-14 [#73079] Migrate project to KiCad 8. Clean DRCs
2025-02-14 [#73079] Update symbols, clean ERC
2025-02-14 [#73079] Fix DSC557-0343FI1 symbol causing ERC violation
2025-03-21 Add SoM size
2025-05-02 Update component mpn in hotareas
2025-05-09 [#75088] Improve footprint of PI3HDX511DZLE
2025-05-09 [#75091] Fix power monitor DNP configuration
2025-05-09 [#75090] Modify default JTAG chain
2025-05-09 [#76827] Update PolarFire MPN. Add test points. Modify DEVRST_N sequence. Bump revision
2025-05-09 [#76827] Fix C_47n_0402 MPN
2025-05-09 [#76827] Change position of GND testpoint
2025-05-09 [#77309] Fix solder mask bridging and clean DRC
2025-05-21 README: Add photo
2025-05-26 [#77565] Update assets
2025-06-27 Add local CI
2025-07-28 [#80745] HDMI DC coupling, KiCAD 9 bump + DRC fixes

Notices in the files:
parts and their libraries:
License: Apache-2.0
